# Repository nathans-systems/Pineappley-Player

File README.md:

# Pineappley-Player
My Open-Source, Custom built MP3 Player.
Using an ESP32-S3-Zero, cheap, available parts and a custom PCB I designed I've built a reliable and high quality audio playing MP3 Player.

## Hardware
- ESP32-S3-Zero
- 1.3 Inch I2C Oled
- Rotary Encoder
- TFT Micro SD Card Module
- KCX Bluetooth Emmiter
- TP4056 Charging Module
- MT3608 Boots Converter
- GY-PCM5102A
- 1800mah lithium battery
- Power Switch

## Key Features
- High Quality Audio
- Headphone Out
- Bluetooth Connectivity
- Micro SD card reader
- Rechargeable Battery

## Programming
The firmware is built on the PlatformIO and Arduino Framework.
You can upload and edit the firmware using Arduino C++ and flashing the ESP via the USB-C port under the OLED.

## PCB
I designed the PCB myself in KICAD. It features many through hole areas for each module, smd contacts for the KCX module and battery resistors and encoder capacitors.

## How Does it Work?
After loading your MP3 Files onto the SD card, the files are read over SPI to the ESP. After decoding, the PCM signal is sent over I2S to the PCM5102. The PCM5102 converts the digital audio to analog which can be read by the KCX Emitter.
The Pineappley Player utilises both cores of the ESP32-S3, forcing all audio tasks to core 0 to ensure clean audio as all other tasks such as drawing to the screen can run on core 1.

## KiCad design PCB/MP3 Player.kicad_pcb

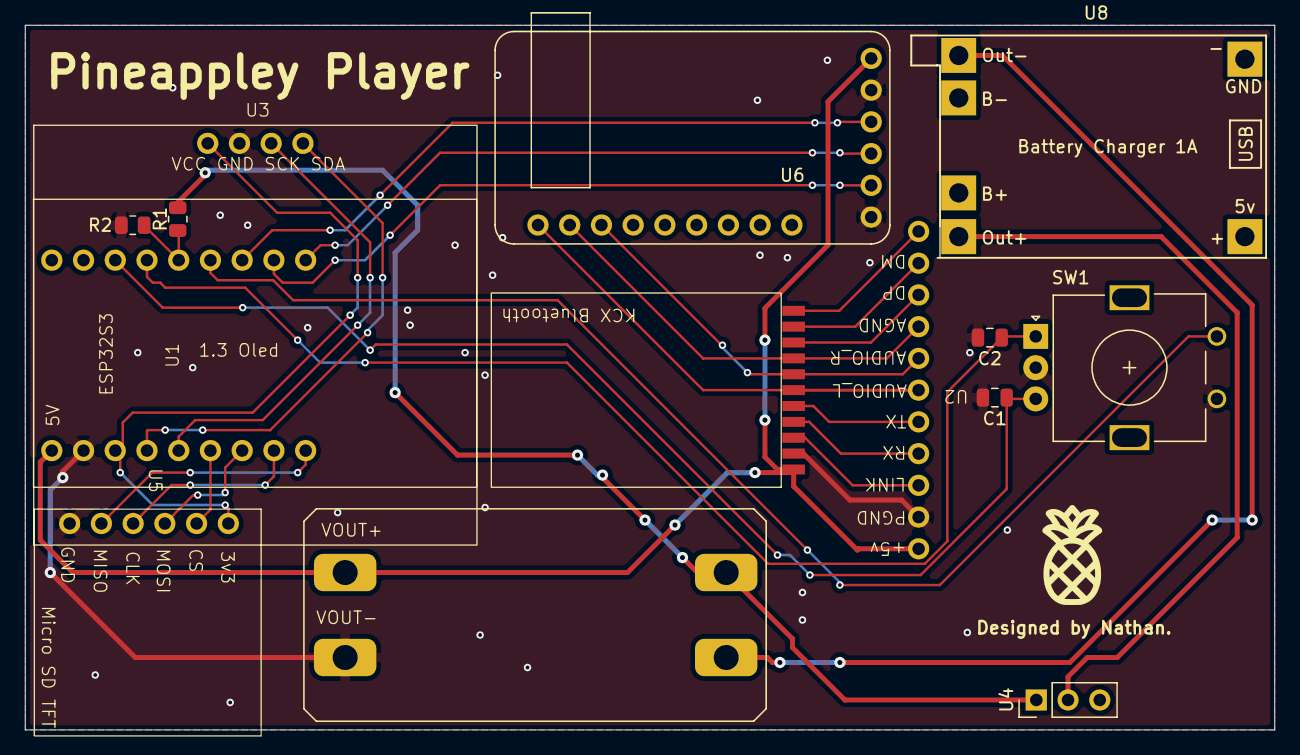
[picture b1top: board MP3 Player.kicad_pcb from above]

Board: 2 copper layers, 100.0 x 56.4 mm, 13 parts (0 on the bottom side), 22 nets.

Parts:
C1, C2: 100nF; C_0805_2012Metric
R1, R2: 10K; R_0805_2012Metric
SW1: RotaryEncoder_Switch; RotaryEncoder_Alps_EC11E_Vertical_H20mm
U1: ESP32S3 MINI
U2: KCX Bluetooth
U3: 1.3 Oled
U4: PinHeader_1x03_P2.54mm_Vertical
U5: TFT MicroSD Module
U6: GY-PCM5102
U7: hw-045
U8: TP4056-18650

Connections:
+5V: U1.1 (5V), U2.1 (5V), U6.1 (VIN), U7.1 (VOUT+)
BAT+ OUT: R1.1, R2.2, U1.14 (GPIO11)
GND: C1.2, C2.2, R2.1, SW1.C, SW1.S2, U1.2 (GND), U2.2 (PGND), U3.2 (GND), U5.1 (GND), U6.2 (GND), U6.6 (SCK), U7.2 (VOUT-)
unnamed: U1.3 (3V3_OUT), U3.1 (VCC), U5.6 (3V3)
unnamed: U1.4 (GPIO1), U3.4 (SDA)
unnamed: U1.5 (GPIO2), U3.3 (SCK)
unnamed: U1.6 (GPIO3), U5.5 (CS)
unnamed: U1.7 (GPIO4), U5.4 (MOSI)
unnamed: U1.8 (GPIO5), U5.3 (CLK)
unnamed: U1.9 (GPIO6), U5.2 (MISO)
unnamed: U1.10 (GPIO7), U6.4 (DIN)
unnamed: U1.11 (GPIO8), U6.5 (BCK)
unnamed: U1.12 (GPIO9), U6.3 (LRCK)
unnamed: SW1.S1, U1.13 (GPIO10)
unnamed: C2.1, SW1.A, U1.15 (GPIO12)
unnamed: C1.1, SW1.B, U1.16 (GPIO13)
unnamed: U2.8 (AGND), U6.14 (AGND)
unnamed: U2.6 (AUDIO_L), U6.15 (LROUT)
unnamed: U2.7 (AUDIO_R), U6.13 (ROUT)
unnamed: U4.2 (IN), U8.1 (OUT+)
unnamed: R1.2, U4.1 (OUT), U7.3 (VIN+)
unnamed: U7.4 (VIN-), U8.4 (OUT-)
